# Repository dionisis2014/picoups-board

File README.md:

#  PicoUPS - Board
A Raspberry PI compatible Uninterruptible Power Supply (board files).

## About
This repo contains the PicoUPS board schematics and layout as a KiCad project.

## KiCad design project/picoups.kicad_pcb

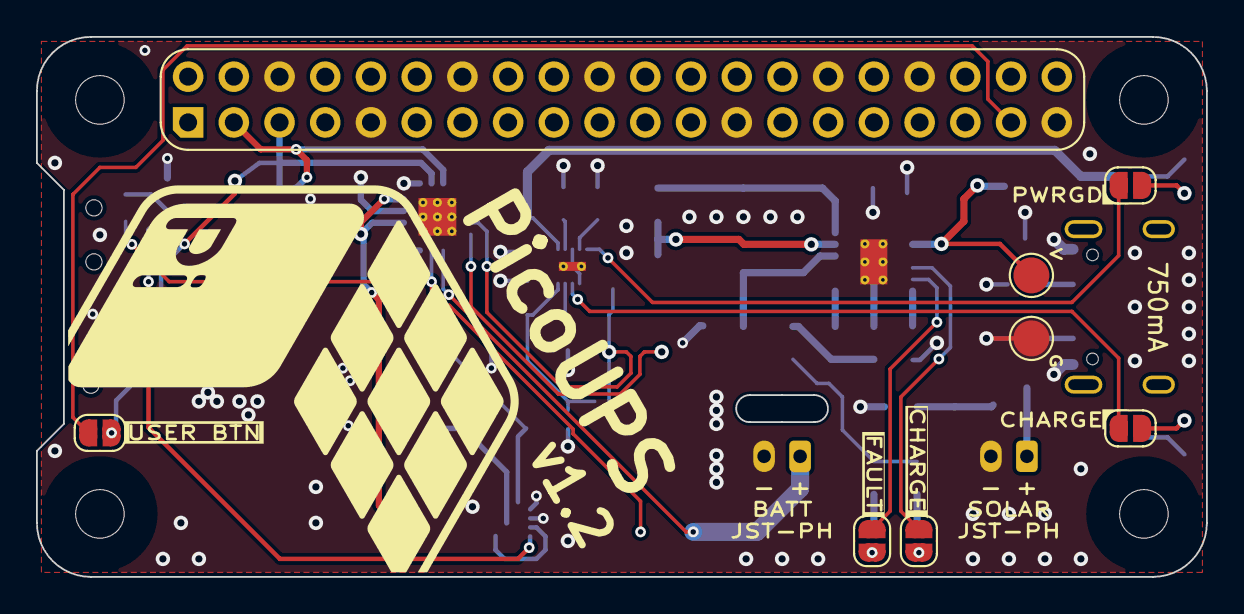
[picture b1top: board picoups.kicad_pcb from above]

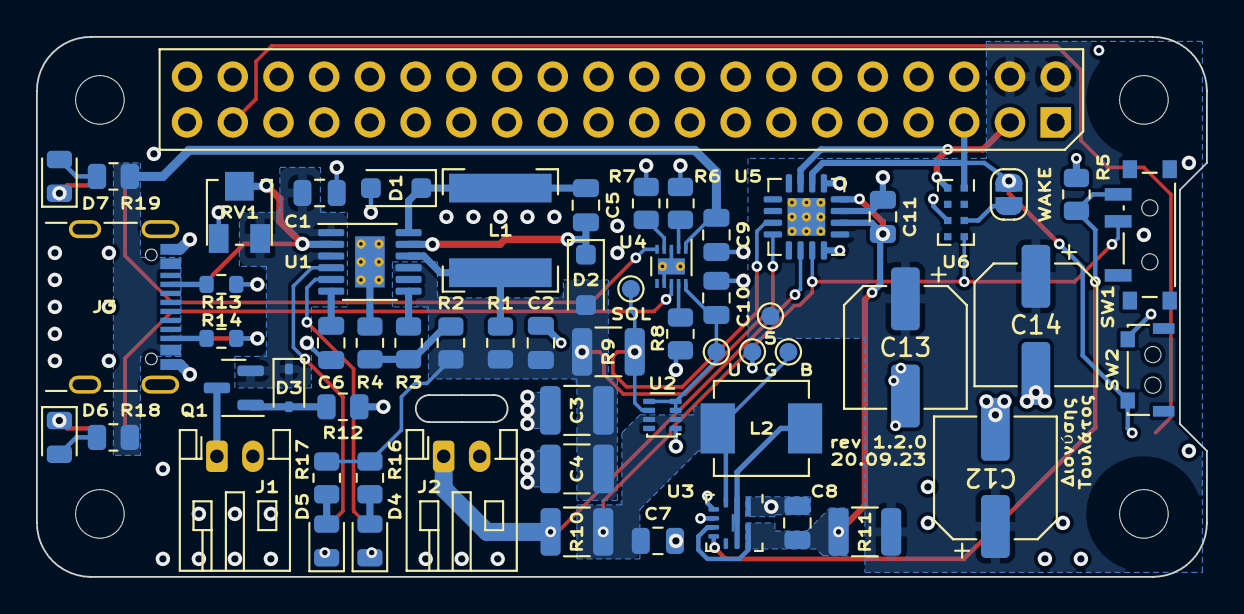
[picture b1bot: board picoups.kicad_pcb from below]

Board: 4 copper layers, 65.0 x 30.0 mm, 68 parts (60 on the bottom side), 42 nets.

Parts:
C1, C2, C7: 10uF; C_0805_2012Metric
C3, C4: 47uF; C_1210_3225Metric
C5, C6, C9, C10: 1uF; C_0805_2012Metric
C8, C11: 22uF; C_0805_2012Metric
C12: 270uF; CP_Elec_6.3x5.8
C13, C14: 470uF; CP_Elec_6.3x7.7
D1, D2: 30V@3A; D_SOD-123F
D3: 11V@300mW; D_SOD-323
D4: FAULT; LED_0805_2012Metric
D5, D6: CHRG; LED_0805_2012Metric
D7: PWRGD; LED_0805_2012Metric
J1: VIN; JST_PH_S2B-PH-K_1x02_P2.00mm_Horizontal
J2: BATT; JST_PH_S2B-PH-K_1x02_P2.00mm_Horizontal
J3: USB_C_Receptacle; USB_C_Receptacle_GCT_USB4105-xx-A_16P_TopMnt_Horizontal
J4: Conn_02x20_Odd_Even; PinSocket_2x20_P2.54mm_Vertical
JP1, JP6: USER; SolderJumper-2_P1.3mm_Open_RoundedPad1.0x1.5mm
JP2: FAULT; SolderJumper-2_P1.3mm_Open_RoundedPad1.0x1.5mm
JP3, JP4: CHRG; SolderJumper-2_P1.3mm_Open_RoundedPad1.0x1.5mm
JP5: PWRGD; SolderJumper-2_P1.3mm_Open_RoundedPad1.0x1.5mm
L1: 7.6uH; L_Bourns-SRN6028
L2: 1uH; L_Vishay_IHLP-2020
Q1: Q_PMOS_GSD; SOT-23
R1: 0.066; R_0805_2012Metric
R2: 80k; R_0805_2012Metric
R3: 185k; R_0805_2012Metric
R4: 330k; R_0805_2012Metric
R5: 1M; R_0805_2012Metric
R6: 720; R_0805_2012Metric
R7: 2k; R_0805_2012Metric
R8: 10k; R_0805_2012Metric
R9, R10, R11: 0.05; R_1210_3225Metric
R12: 20k; R_0805_2012Metric
R13, R14: 5.1k; R_0603_1608Metric
R16, R17: 260; R_0805_2012Metric
R18, R19: 1k; R_0805_2012Metric
RV1: 10k; Potentiometer_Bourns_3313J-1_Vertical
SW1: SW_5V; SW_SPDT_PCM12
SW2: SW_USER; SW_Push
TP1: VIN_REG; TestPoint_Pad_D2.0mm
TP2: GND; TestPoint_Pad_D2.0mm
TP3, TP9: 5V; TestPoint_Pad_D1.0mm
TP5: GND; TestPoint_Pad_D1.0mm
TP6, TP8: VBAT; TestPoint_Pad_D1.0mm
U1: LT3652EMSE; MSOP-12-1EP_3x4mm_P0.65mm_EP1.65x2.85mm_ThermalVias
U2: TPS2116; SOT-583-8
U3: TPS61235P
U4: BQ24040; WSON-10-1EP_2x2mm_P0.5mm
U5: INA3221; Texas_RGV_S-PVQFN-N16_EP2.1x2.1mm_ThermalVias
U6: M41T62; LCC-8

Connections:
5V: C12.1, C13.1, C14.1, J4.2, J4.4, R11.2, TP3.1, U5.1 (IN-3)
5V+: C8.1, C11.1, R11.1, U3.6 (FB), U3.9 (VOUT), U5.2 (IN+3), U5.4 (VS)
/Solar Panel Supply/BOOST: C5.2, D2.1 (K), U1.11 (BOOST)
/Solar Panel Supply/CHRG: JP3.1 (A), U1.4 (~CHRG)
/Solar Panel Supply/FAULT: JP2.1 (A), U1.5 (~FAULT)
/Solar Panel Supply/SENSE: L1.2, R1.1, U1.10 (SENSE)
/Solar Panel Supply/SW: C5.1, D1.1 (K), L1.1, U1.12 (SW)
/Solar Panel Supply/VIN: C1.1, D3.1 (K), Q1.2 (S), RV1.1, U1.1 (V_{IN}), U1.3 (~SHDN)
/Status LEDs/USB_CHRG: JP4.1 (A), U4.8 (~CHG)
/Status LEDs/USB_PWRGD: JP5.1 (A), U4.5 (~PG)
GND: C1.2, C2.2, C3.2, C4.2, C6.2, C7.2, C8.2, C9.1, C10.2, C11.2, C12.2, C13.2, C14.2, D1.2 (A), J1.2, J2.2, J3.A1 (GND), J3.A12 (GND), J3.B1 (GND), J3.B12 (GND), J4.6, J4.9, J4.14, J4.20, J4.25, J4.30, J4.34, J4.39, R4.2, R5.1, R6.1, R7.1, R8.1, R12.2, R13.1, R14.1, RV1.3, SW2.1, TP2.1, TP5.1, U1.13 (GND), U2.1 (GND), U3.1 (PGND), U3.4 (CC), U3.5 (AGND), U4.3 (VSS), U4.7 (ISET2), U5.3 (GND), U5.5 (A0), U5.16 (VPU), U5.17 (EP), U6.3 (VSS)
unnamed: D3.2 (A), Q1.1 (G), R12.1
unnamed: D4.2 (A), R16.1
unnamed: D4.1 (K), JP2.2 (B)
unnamed: D5.2 (A), R17.1
unnamed: D5.1 (K), JP3.2 (B)
unnamed: D6.2 (A), R18.1
unnamed: D6.1 (K), JP4.2 (B)
unnamed: D7.2 (A), R19.1
unnamed: D7.1 (K), JP5.2 (B)
unnamed: J1.1, Q1.3 (D)
unnamed: J3.A5 (CC1), R13.2
unnamed: J3.B5 (CC2), R14.2
unnamed: J4.37, JP1.2 (B)
unnamed: R2.1, R3.2, R4.1
unnamed: R5.2, SW1.3 (C), U3.7 (EN)
unnamed: C6.1, U1.6 (TIMER)
unnamed: R3.1, U1.7 (V_{FB})
unnamed: L2.2, U3.2 (SW)
unnamed: R6.2, U4.2 (ISET)
unnamed: R7.2, U4.4 (PRE-TERM)
unnamed: R8.2, U4.9 (TS)
SCL: J4.5, JP1.1 (A), JP6.2 (B), SW2.2, U5.6 (SCL), U6.8 (SCL)
SDA: J4.3, U5.7 (SDA), U6.1 (SDA)
USB_5V: C9.2, J3.A4 (VBUS), J3.A9 (VBUS), J3.B4 (VBUS), J3.B9 (VBUS), R18.2, R19.2, U4.1 (IN)
VBAT+: C7.1, L2.1, R10.2, SW1.2 (B), TP6.1, U2.2 (VOUT), U2.7 (VOUT), U3.3 (VIN), U5.15 (IN+2), U6.5 (VCC)
VBAT-: J2.1, R10.1, U5.14 (IN-2)
VBAT_SOL+: C2.1, C3.1, C4.1, D2.2 (A), R1.2, R2.2, R9.1, R16.2, R17.2, U1.9 (BAT), U5.12 (IN+1)
VBAT_SOL-: R9.2, TP8.1, U2.6 (VIN2), U5.11 (IN-1)
VBAT_USB: C10.1, TP9.1, U2.3 (VIN1), U2.4 (PR1), U2.5 (MODE), U4.10 (OUT)
VIN_REG: RV1.2, TP1.1, U1.2 (V_{IN_REG})
WAKEUP: JP6.1 (A), U6.6 (~IRQ/OUT)

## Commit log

2023-04-28 Added icon
2023-04-29 Cleanup
2023-04-29 Created basic schematic
2023-04-29 Update gitignore
2023-04-29 Added values and footprints
2023-04-29 Added PCB constrains PCBWay
2023-04-30 First board prototype
2023-04-30 Fix .gitignore
2023-04-30 Dropped fp-info-cache from tracking
2023-05-02 Rearrange based on available parts
2023-06-05 Fixed incorrect VIN_REG divider
2023-06-12 Added boost converter and power monitor
2023-06-12 Added components
2023-06-12 Semi final layout
2023-06-12 Flip board
2023-06-12 Ready for final check
2023-06-13 Final version of this revision
2023-07-19 Revision 1 single page
2023-07-20 Revision 1 multi-page
2023-07-20 Added user button
2023-07-20 Added symbol annotations
2023-07-20 Added footprints
2023-07-21 Fix BQ2404 footprint
2023-07-21 Fixed footprints
2023-07-21 Basic layout
2023-07-23 Fixed footprint
2023-07-23 First layout of PCB
2023-07-25 Semi-final arrangement
2023-07-25 Added NC pin
2023-07-25 Changed to thermal vias footprint
2023-07-25 Fixed pin numbering
2023-07-25 Final layout
2023-07-27 Labels final position
2023-07-27 Added labels
2023-07-27 Added final labels
2023-07-27 Final touches
2023-07-27 Final revision
2023-07-28 Tweak for fab
2023-07-28 Exports for fab
2023-08-27 Fixed incorrect mirrored pads
2023-08-27 Fixed mirrored RTC footprint
2023-08-27 Minor improvements
2023-08-27 Semi final v1.1
2023-09-16 Revision 1.1.1
2023-09-18 Fixed solar status LEDs wrong VBAT
2023-09-18 Moved 5V supply
2023-09-18 Dimmed the USB status LEDs (again)
2023-09-18 Added RTC wake
2023-09-18 Added output capacitors
2023-09-18 Moved main logo up a bit
2023-09-19 Polishing touches~
2023-09-19 Revision 1.2.0
2023-09-20 Fix revision number
2023-09-20 Export Gerber files
2023-10-17 Move name and 5V plane
2024-02-10 Added HTML BOM
